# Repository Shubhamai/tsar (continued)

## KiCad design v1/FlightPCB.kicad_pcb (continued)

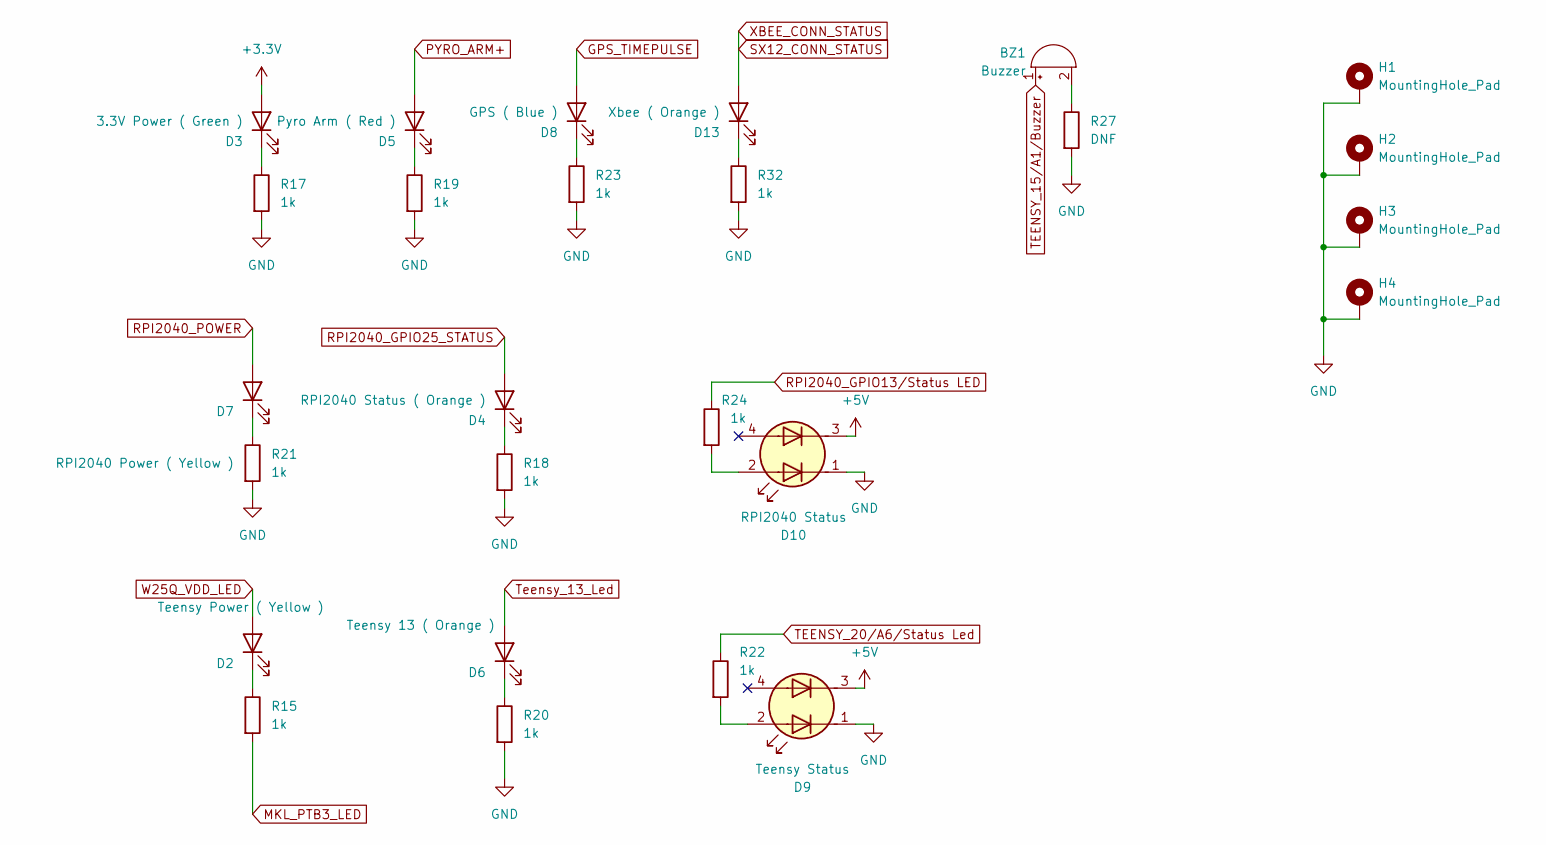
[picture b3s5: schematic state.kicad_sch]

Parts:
BZ1: Buzzer; Buzzer_CUI_CPT-9019S-SMT
D2: Teensy Power ( Yellow ); LED_0402_1005Metric
D3: 3.3V Power ( Green ); LED_0402_1005Metric
D4: RPI2040 Status ( Orange ); LED_0402_1005Metric
D5: Pyro Arm ( Red ); LED_0402_1005Metric
D6: Teensy 13 ( Orange ); LED_0402_1005Metric
D7: RPI2040 Power ( Yellow ); LED_0402_1005Metric
D8: GPS ( Blue ); LED_0402_1005Metric
D9: Teensy Status; IN-PI22TAT5R5G5B
D10: RPI2040 Status; IN-PI22TAT5R5G5B
D13: Xbee ( Orange ); LED_0402_1005Metric
H1, H2, H3, H4: MountingHole_Pad; MountingHole_2.7mm_M2.5_Pad_Via
R15, R17, R18, R19, R20, R21, R22, R23, R24, R32: 1k; R_0603_1608Metric
R27: DNF; R_0603_1608Metric

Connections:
+3.3V: D3.2 (A); also elsewhere on the board
+5V: D9.3 (A2), D10.3 (A2); also elsewhere on the board
BARO_SCK/Teensy: D6.2 (A); also elsewhere on the board
BatteryTerminal-: D9.1 (A1), D10.1 (A1), H1.1, H2.1, H3.1, H4.1, R17.2, R18.2, R19.2, R20.2, R21.2, R23.2, R27.2, R32.2; also elsewhere on the board
GPS_TIMEPULSE: D8.2 (A); also elsewhere on the board
MKL_PTB3_LED: R15.2; also elsewhere on the board
unnamed: BZ1.2 (-), R27.1
unnamed: D2.1 (K), R15.1
unnamed: D3.1 (K), R17.1
unnamed: D4.1 (K), R18.1
unnamed: D5.1 (K), R19.1
unnamed: D6.1 (K), R20.1
unnamed: D7.1 (K), R21.1
unnamed: D8.1 (K), R23.1
unnamed: D9.2 (K1), R22.2
unnamed: D10.2 (K1), R24.2
unnamed: D13.1 (K), R32.1
PYRO_ARM+: D5.2 (A); also elsewhere on the board
RPI2040_GPIO13/Status LED: R24.1; also elsewhere on the board
RPI2040_GPIO25_STATUS: D4.2 (A); also elsewhere on the board
RPI2040_POWER: D7.2 (A); also elsewhere on the board
SX12_CONN_STATUS: D13.2 (A); also elsewhere on the board
TEENSY_15/A1/Buzzer: BZ1.1 (+); also elsewhere on the board
TEENSY_20/A6: R22.1; also elsewhere on the board
W25Q_VDD_LED: D2.2 (A); also elsewhere on the board

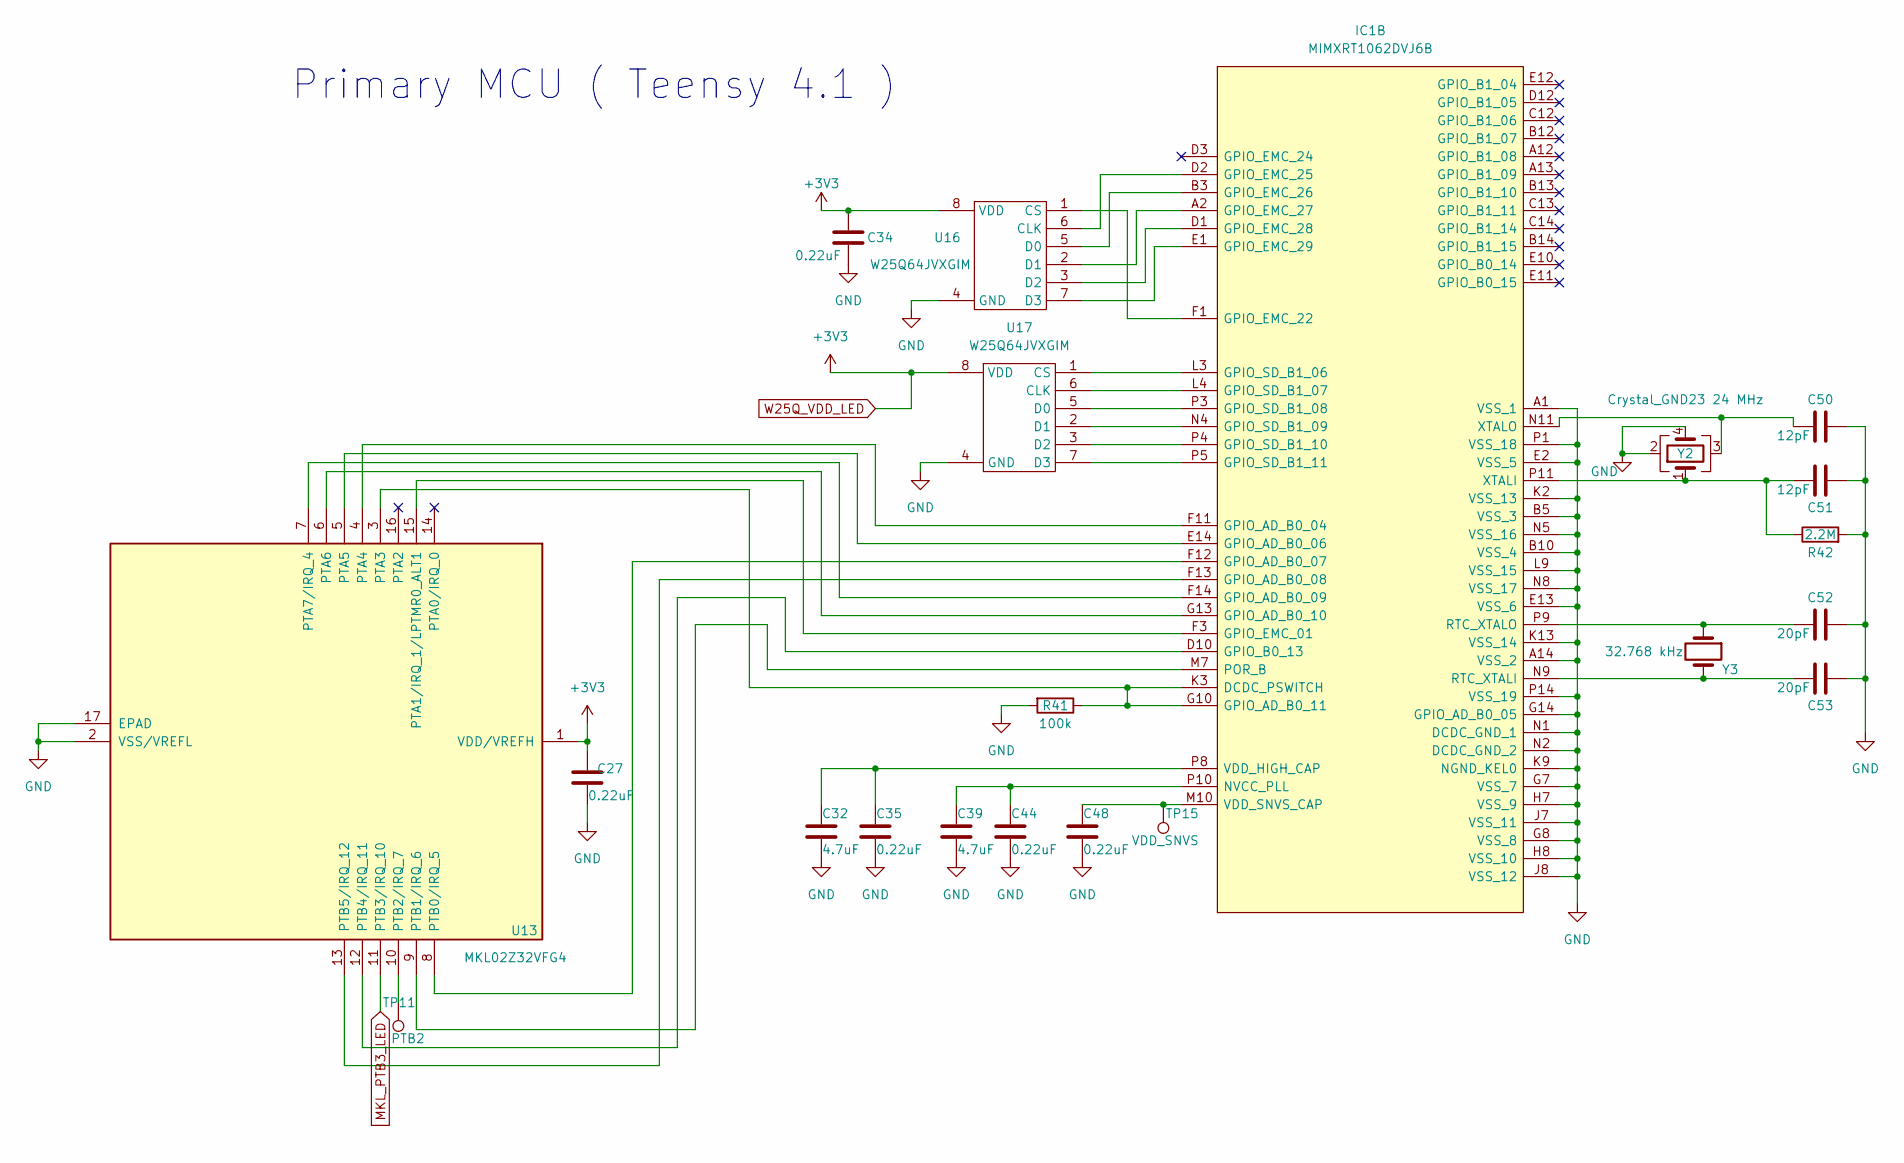
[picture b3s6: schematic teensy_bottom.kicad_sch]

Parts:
C27, C34, C35, C44, C48: 0.22uF; C_0402_1005Metric
C32, C39: 4.7uF; C_0603_1608Metric
C50, C51: 12pF; C_0402_1005Metric
C52, C53: 20pF; C_0402_1005Metric
IC1: MIMXRT1062DVJ6B; BGA196C80P14X14_1200X1200X152; Mouser Part Number 771-MIMXRT1062DVJ6B
R41: 100k; R_0603_1608Metric
R42: 2.2M; R_0603_1608Metric
TP11: PTB2; TestPoint_Pad_D1.0mm
TP15: VDD_SNVS; TestPoint_Pad_D1.0mm
U13: MKL02Z32VFG4; QFN-16-1EP_3x3mm_P0.5mm_EP1.9x1.9mm
U16, U17: W25Q64JVXGIM; XSON8_4x4mm
Y2: Crystal_GND23 24 MHz; Crystal_SMD_Abracon_ABM3B-4Pin_5.0x3.2mm
Y3: 32.768 kHz; Crystal_SMD_2012-2Pin_2.0x1.2mm

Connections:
BatteryTerminal-: C27.2, C32.2, C34.2, C35.2, C39.2, C44.2, C48.2, C50.2, C51.2, C52.2, C53.2, IC1.A1 (VSS_1), IC1.A14 (VSS_2), IC1.B5 (VSS_3), IC1.B10 (VSS_4), IC1.E2 (VSS_5), IC1.E13 (VSS_6), IC1.G7 (VSS_7), IC1.G8 (VSS_8), IC1.G14 (GPIO_AD_B0_05), IC1.H7 (VSS_9), IC1.H8 (VSS_10), IC1.J7 (VSS_11), IC1.J8 (VSS_12), IC1.K2 (VSS_13), IC1.K9 (NGND_KEL0), IC1.K13 (VSS_14), IC1.L9 (VSS_15), IC1.N1 (DCDC_GND_1), IC1.N2 (DCDC_GND_2), IC1.N5 (VSS_16), IC1.N8 (VSS_17), IC1.P1 (VSS_18), IC1.P14 (VSS_19), R41.2, R42.2, U13.2 (VSS/VREFL), U13.17 (EPAD), U16.4 (GND), U17.4 (GND), Y2.2, Y2.4; also elsewhere on the board
MKL_PTB3_LED: U13.11 (PTB3/IRQ_10); also elsewhere on the board
unnamed: IC1.G10 (GPIO_AD_B0_11), IC1.K3 (DCDC_PSWITCH), R41.1, U13.3 (PTA3)
unnamed: IC1.F11 (GPIO_AD_B0_04), U13.4 (PTA4)
unnamed: IC1.E14 (GPIO_AD_B0_06), U13.5 (PTA5)
unnamed: IC1.F12 (GPIO_AD_B0_07), U13.8 (PTB0/IRQ_5)
unnamed: IC1.F13 (GPIO_AD_B0_08), U13.13 (PTB5/IRQ_12)
unnamed: IC1.F14 (GPIO_AD_B0_09), U13.7 (PTA7/IRQ_4)
unnamed: IC1.G13 (GPIO_AD_B0_10), U13.6 (PTA6)
unnamed: IC1.D10 (GPIO_B0_13), U13.12 (PTB4/IRQ_11)
unnamed: IC1.F3 (GPIO_EMC_01), U13.15 (PTA1/IRQ_1/LPTMR0_ALT1)
unnamed: IC1.F1 (GPIO_EMC_22), U16.1 (CS)
unnamed: IC1.D2 (GPIO_EMC_25), U16.6 (CLK)
unnamed: IC1.B3 (GPIO_EMC_26), U16.5 (D0)
unnamed: IC1.A2 (GPIO_EMC_27), U16.2 (D1)
unnamed: IC1.D1 (GPIO_EMC_28), U16.3 (D2)
unnamed: IC1.E1 (GPIO_EMC_29), U16.7 (D3)
unnamed: IC1.L3 (GPIO_SD_B1_06), U17.1 (CS)
unnamed: IC1.L4 (GPIO_SD_B1_07), U17.6 (CLK)
unnamed: IC1.P3 (GPIO_SD_B1_08), U17.5 (D0)
unnamed: IC1.N4 (GPIO_SD_B1_09), U17.2 (D1)
unnamed: IC1.P4 (GPIO_SD_B1_10), U17.3 (D2)
unnamed: IC1.P5 (GPIO_SD_B1_11), U17.7 (D3)
unnamed: C39.1, C44.1, IC1.P10 (NVCC_PLL)
unnamed: IC1.M7 (POR_B), U13.9 (PTB1/IRQ_6)
unnamed: C53.1, IC1.N9 (RTC_XTALI), Y3.2
unnamed: C52.1, IC1.P9 (RTC_XTALO), Y3.1
unnamed: C32.1, C35.1, IC1.P8 (VDD_HIGH_CAP)
unnamed: C48.1, IC1.M10 (VDD_SNVS_CAP), TP15.1
unnamed: C51.1, IC1.P11 (XTALI), R42.1, Y2.1
unnamed: C50.1, IC1.N11 (XTALO), Y2.3
unnamed: TP11.1, U13.10 (PTB2/IRQ_7)
W25Q_VDD_LED: C27.1, C34.1, U13.1 (VDD/VREFH), U16.8 (VDD), U17.8 (VDD); also elsewhere on the board

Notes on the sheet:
Primary MCU ( Teensy 4.1 )

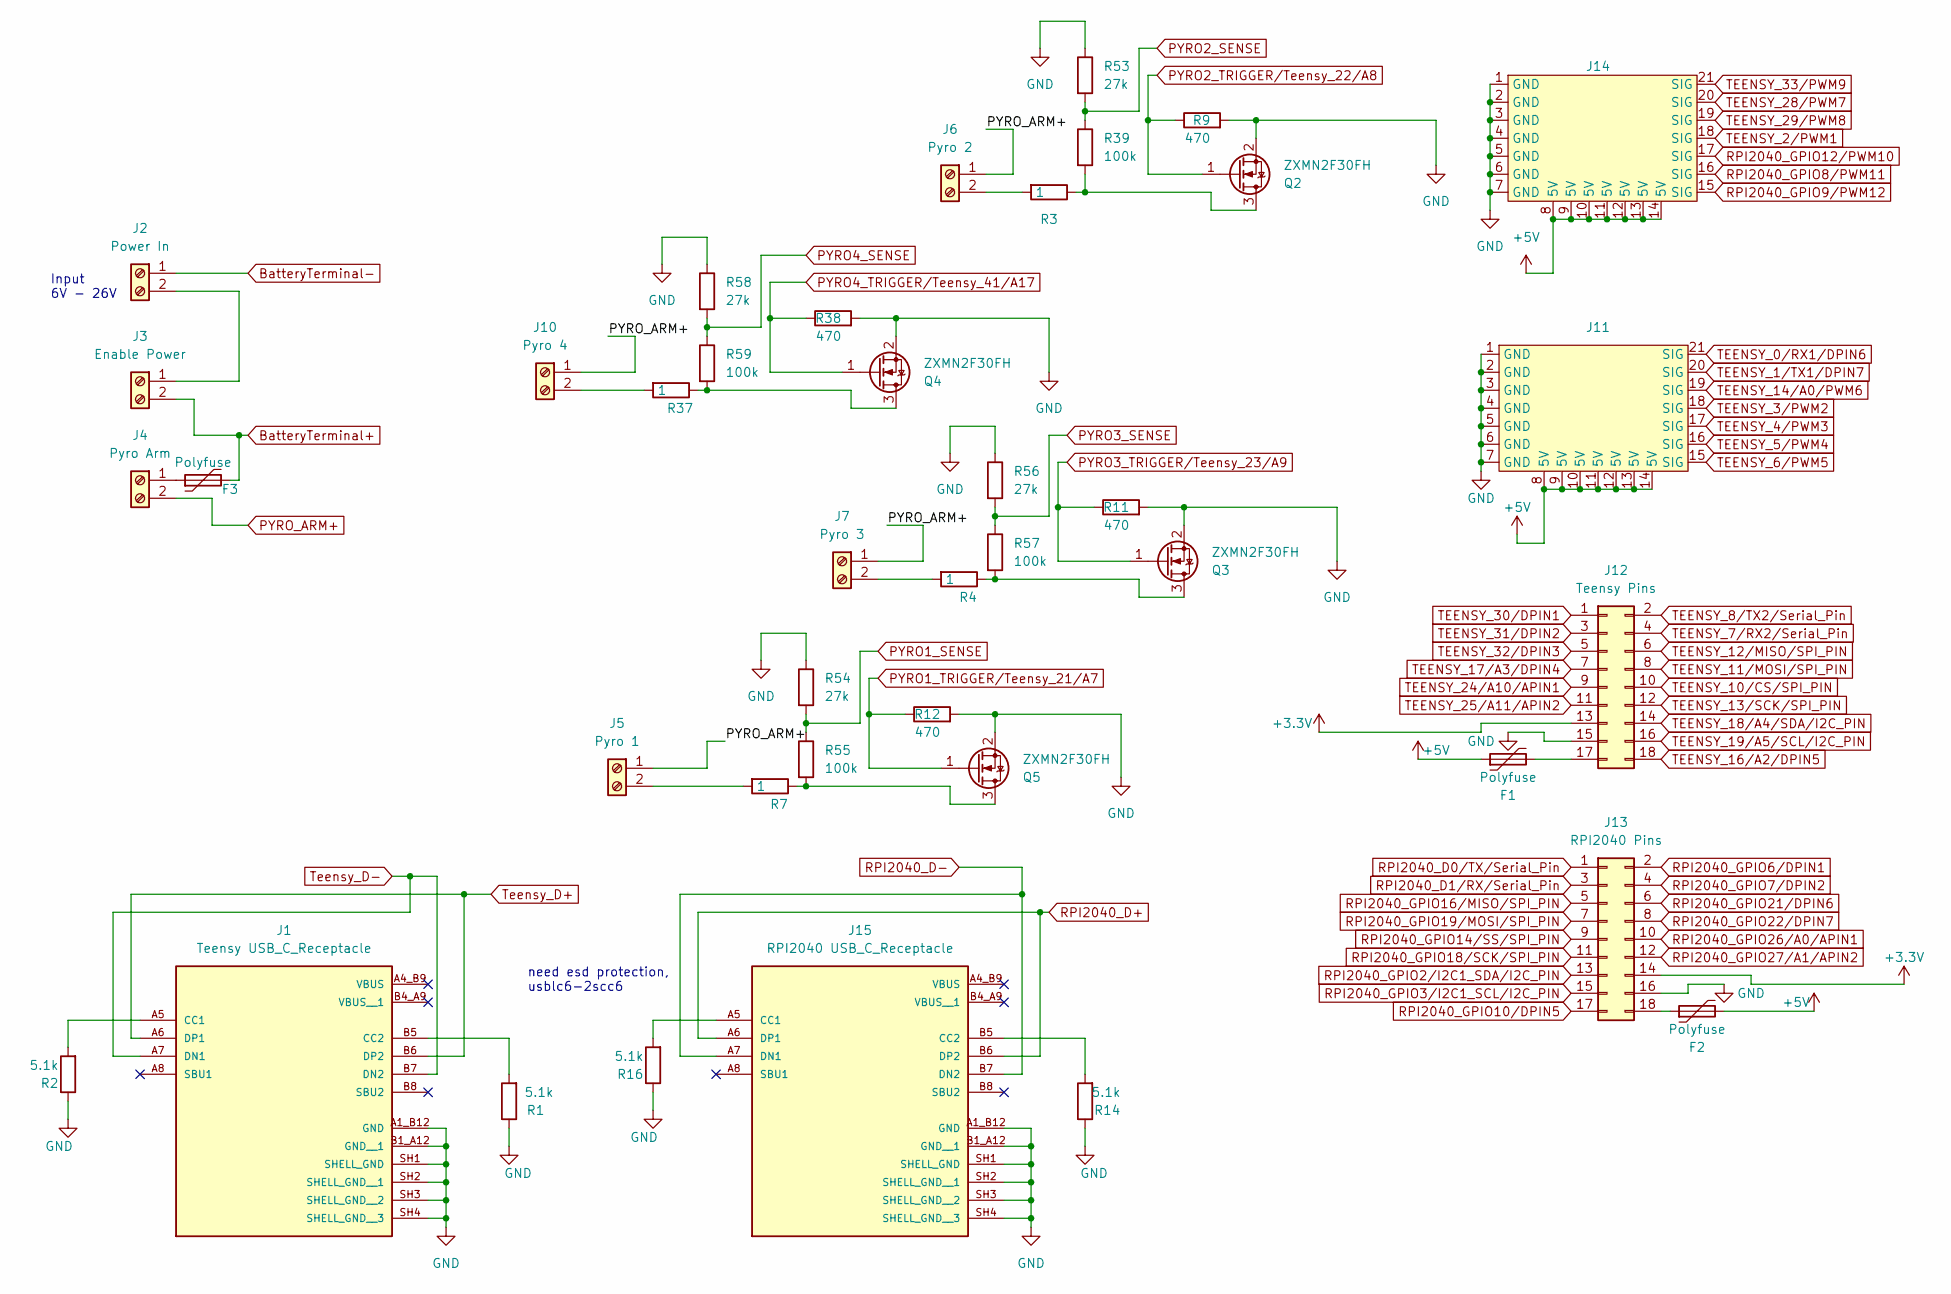
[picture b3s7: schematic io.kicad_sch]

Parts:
F1, F2: Polyfuse; Fuse_1206_3216Metric
F3: Polyfuse; Fuse_1812_4532Metric
J1: Teensy USB_C_Receptacle; GCT_USB4105-GF-A; PARTREV B3
J2: Power In; TerminalBlock_Phoenix_PT-1,5-2-5.0-H_1x02_P5.00mm_Horizontal
J3: Enable Power; TerminalBlock_Phoenix_PT-1,5-2-5.0-H_1x02_P5.00mm_Horizontal
J4: Pyro Arm; TerminalBlock_Phoenix_PT-1,5-2-5.0-H_1x02_P5.00mm_Horizontal
J5: Pyro 1; TerminalBlock_Phoenix_PT-1,5-2-5.0-H_1x02_P5.00mm_Horizontal
J6: Pyro 2; TerminalBlock_Phoenix_PT-1,5-2-5.0-H_1x02_P5.00mm_Horizontal
J7: Pyro 3; TerminalBlock_Phoenix_PT-1,5-2-5.0-H_1x02_P5.00mm_Horizontal
J10: Pyro 4; TerminalBlock_Phoenix_PT-1,5-2-5.0-H_1x02_P5.00mm_Horizontal
J11: PinHeader_3x05_P2.54mm_Vertical_Left
J12: Teensy Pins; PinSocket_2x09_P2.54mm_Vertical
J13: RPI2040 Pins; PinSocket_2x09_P2.54mm_Vertical
J14: PinHeader_3x05_P2.54mm_Vertical_Right
J15: RPI2040 USB_C_Receptacle; GCT_USB4105-GF-A; PARTREV B3
Q2, Q3, Q4, Q5: ZXMN2F30FH; SOT-23
R1, R2, R14, R16: 5.1k; R_0603_1608Metric
R3, R4, R7, R37: 1; R_0603_1608Metric
R9, R11, R12, R38: 470; R_0603_1608Metric
R39, R55, R57, R59: 100k; R_0603_1608Metric
R53, R54, R56, R58: 27k; R_0603_1608Metric

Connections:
+3.3V: J12.13, J13.14; also elsewhere on the board
+5V: F1.1, F2.2, J11.8 (5V), J11.9 (5V), J11.10 (5V), J11.11 (5V), J11.12 (5V), J11.13 (5V), J11.14 (5V), J14.8 (5V), J14.9 (5V), J14.10 (5V), J14.11 (5V), J14.12 (5V), J14.13 (5V), J14.14 (5V); also elsewhere on the board
BARO_MISO/Teensy: J12.6; also elsewhere on the board
BARO_MOSI/Teensy: J12.8; also elsewhere on the board
BARO_SCK/Teensy: J12.12; also elsewhere on the board
BatteryTerminal+: F3.2, J3.2; also elsewhere on the board
BatteryTerminal-: J1.A1_B12 (GND), J1.B1_A12 (GND__1), J1.SH1 (SHELL_GND), J1.SH2 (SHELL_GND__1), J1.SH3 (SHELL_GND__2), J1.SH4 (SHELL_GND__3), J2.1, J11.1 (GND), J11.2 (GND), J11.3 (GND), J11.4 (GND), J11.5 (GND), J11.6 (GND), J11.7 (GND), J12.15, J13.16, J14.1 (GND), J14.2 (GND), J14.3 (GND), J14.4 (GND), J14.5 (GND), J14.6 (GND), J14.7 (GND), J15.A1_B12 (GND), J15.B1_A12 (GND__1), J15.SH1 (SHELL_GND), J15.SH2 (SHELL_GND__1), J15.SH3 (SHELL_GND__2), J15.SH4 (SHELL_GND__3), Q2.2 (S), Q3.2 (S), Q4.2 (S), Q5.2 (S), R1.1, R2.1, R9.2, R11.2, R12.2, R14.1, R16.1, R38.2, R53.1, R54.1, R56.1, R58.1; also elsewhere on the board
unnamed: J1.A5 (CC1), R2.2
unnamed: J1.B5 (CC2), R1.2
unnamed: J2.2, J3.1
unnamed: F3.1, J4.1
unnamed: J5.2, R7.2
unnamed: J6.2, R3.2
unnamed: J7.2, R4.2
unnamed: J10.2, R37.2
unnamed: F1.2, J12.17
unnamed: F2.1, J13.18
unnamed: J15.A5 (CC1), R16.2
unnamed: J15.B5 (CC2), R14.2
unnamed: Q2.3 (D), R3.1, R39.2
unnamed: Q3.3 (D), R4.1, R57.2
unnamed: Q4.3 (D), R37.1, R59.2
unnamed: Q5.3 (D), R7.1, R55.2
PYRO1_SENSE: R54.2, R55.1; also elsewhere on the board
PYRO1_TRIGGER/Teensy_21/A7: Q5.1 (G), R12.1; also elsewhere on the board
PYRO2_SENSE: R39.1, R53.2; also elsewhere on the board
PYRO2_TRIGGER/Teensy_22/A8: Q2.1 (G), R9.1; also elsewhere on the board
PYRO3_SENSE: R56.2, R57.1; also elsewhere on the board
PYRO3_TRIGGER/Teensy_23/A9: Q3.1 (G), R11.1; also elsewhere on the board
PYRO4_SENSE: R58.2, R59.1; also elsewhere on the board
PYRO4_TRIGGER/Teensy_41/A17: Q4.1 (G), R38.1; also elsewhere on the board
PYRO_ARM+: J4.2, J5.1, J6.1, J7.1, J10.1; also elsewhere on the board
RPI2040_D0/TX/Serial_Pin: J13.1; also elsewhere on the board
RPI2040_D1/RX/Serial_Pin: J13.3; also elsewhere on the board
RPI2040_D+: J15.A6 (DP1), J15.B6 (DP2); also elsewhere on the board
RPI2040_D-: J15.A7 (DN1), J15.B7 (DN2); also elsewhere on the board
RPI2040_GPIO2/I2C1_SDA/I2C_PIN: J13.13; also elsewhere on the board
RPI2040_GPIO3/I2C1_SCL/I2C_PIN: J13.15; also elsewhere on the board
RPI2040_GPIO6/DPIN1: J13.2; also elsewhere on the board
RPI2040_GPIO7/DPIN2: J13.4; also elsewhere on the board
RPI2040_GPIO8/PWM11: J14.16 (SIG); also elsewhere on the board
RPI2040_GPIO9/PWM12: J14.15 (SIG); also elsewhere on the board
RPI2040_GPIO10/DPIN5: J13.17; also elsewhere on the board
RPI2040_GPIO12/PWM10: J14.17 (SIG); also elsewhere on the board
RPI2040_GPIO14/SS/SPI_PIN: J13.9; also elsewhere on the board
RPI2040_GPIO16/MISO/SPI_PIN: J13.5; also elsewhere on the board
RPI2040_GPIO18/SCK/SPI_PIN: J13.11; also elsewhere on the board
RPI2040_GPIO19/MOSI/SPI_PIN: J13.7; also elsewhere on the board
RPI2040_GPIO21/DPIN6: J13.6; also elsewhere on the board
RPI2040_GPIO22/DPIN7: J13.8; also elsewhere on the board
RPI2040_GPIO26/A0/APIN1: J13.10; also elsewhere on the board
RPI2040_GPIO27/A1/APIN2: J13.12; also elsewhere on the board
TEENSY_0/RX1: J11.21 (SIG); also elsewhere on the board
TEENSY_1/TX1: J11.20 (SIG); also elsewhere on the board
TEENSY_2/PWM1: J14.18 (SIG); also elsewhere on the board
TEENSY_3/PWM2: J11.18 (SIG); also elsewhere on the board
TEENSY_4/PWM3: J11.17 (SIG); also elsewhere on the board
TEENSY_5/PWM4: J11.16 (SIG); also elsewhere on the board
TEENSY_6/PWM5: J11.15 (SIG); also elsewhere on the board
TEENSY_7/RX2/Serial_Pin: J12.4; also elsewhere on the board
TEENSY_8/TX2/Serial_Pin: J12.2; also elsewhere on the board
TEENSY_10/CS/SPI_PIN: J12.10; also elsewhere on the board
TEENSY_14/A0/PWM6: J11.19 (SIG); also elsewhere on the board
TEENSY_16/A2: J12.18; also elsewhere on the board
TEENSY_17/A3: J12.7; also elsewhere on the board
TEENSY_18/A4/SDA/I2C_PIN: J12.14; also elsewhere on the board
TEENSY_19/A5/SCL/I2C_PIN: J12.16; also elsewhere on the board
TEENSY_24/A10: J12.9; also elsewhere on the board
TEENSY_25/A11: J12.11; also elsewhere on the board
TEENSY_28/PWM7: J14.20 (SIG); also elsewhere on the board
TEENSY_29/PWM8: J14.19 (SIG); also elsewhere on the board
TEENSY_30/DPIN1: J12.1; also elsewhere on the board
TEENSY_31/DPIN2: J12.3; also elsewhere on the board
TEENSY_32/DPIN3: J12.5; also elsewhere on the board
TEENSY_33/PWM9: J14.21 (SIG); also elsewhere on the board
Teensy_D+: J1.A6 (DP1), J1.B6 (DP2); also elsewhere on the board
Teensy_D-: J1.A7 (DN1), J1.B7 (DN2); also elsewhere on the board

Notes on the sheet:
need esd protection, usblc6-2scc6
Input 6V - 26V

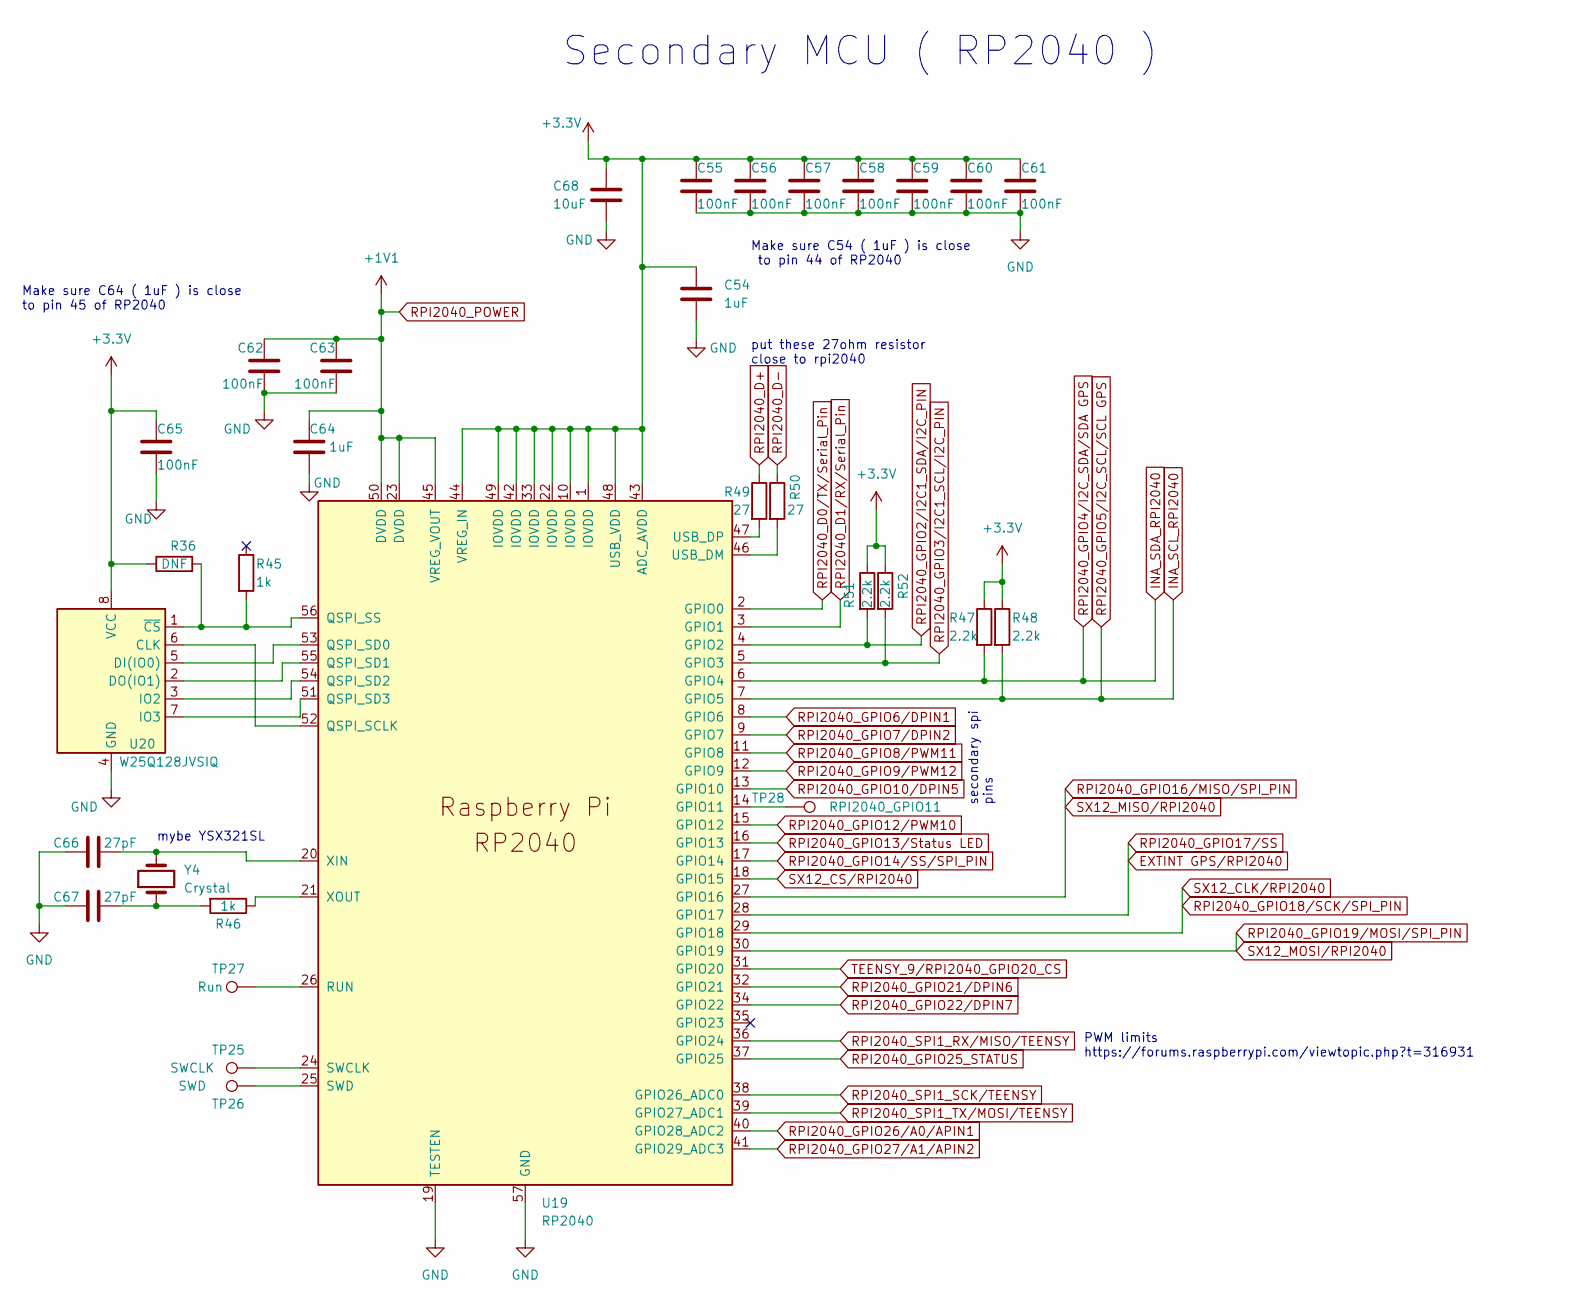
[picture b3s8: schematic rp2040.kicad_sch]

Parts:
C54, C64: 1uF; C_0603_1608Metric
C55, C56, C57, C58, C59, C60, C61, C62, C63, C65: 100nF; C_0603_1608Metric
C66, C67: 27pF; C_0603_1608Metric
C68: 10uF; C_0603_1608Metric
R36: DNF; R_0603_1608Metric
R45, R46: 1k; R_0603_1608Metric
R47, R48, R51, R52: 2.2k; R_0603_1608Metric
R49, R50: 27; R_0603_1608Metric
TP25: SWCLK; TestPoint_Pad_D1.0mm
TP26: SWD; TestPoint_Pad_D1.0mm
TP27: Run; TestPoint_Pad_D1.0mm
TP28: RPI2040_GPIO11; TestPoint_Pad_D1.0mm
U19: RP2040; RP2040-QFN-56
U20: W25Q128JVSIQ; SOIC-8_5.23x5.23mm_P1.27mm
Y4: Crystal; Crystal_SMD_Abracon_ABM8G-4Pin_3.2x2.5mm

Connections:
+3.3V: C54.1, C55.1, C56.1, C57.1, C58.1, C59.1, C60.1, C61.1, C65.1, C68.1, R36.1, R47.1, R48.1, R51.1, R52.1, U19.1 (IOVDD), U19.10 (IOVDD), U19.22 (IOVDD), U19.33 (IOVDD), U19.42 (IOVDD), U19.43 (ADC_AVDD), U19.44 (VREG_IN), U19.48 (USB_VDD), U19.49 (IOVDD), U20.8 (VCC); also elsewhere on the board
BARO_MISO/Teensy: U19.36 (GPIO24); also elsewhere on the board
BARO_MOSI/Teensy: U19.39 (GPIO27_ADC1); also elsewhere on the board
BARO_SCK/Teensy: U19.38 (GPIO26_ADC0); also elsewhere on the board
BatteryTerminal-: C54.2, C55.2, C56.2, C57.2, C58.2, C59.2, C60.2, C61.2, C62.2, C63.2, C64.2, C65.2, C66.1, C67.2, C68.2, U19.19 (TESTEN), U19.57 (GND), U20.4 (GND); also elsewhere on the board
EXTINT GPS/RPI2040: U19.28 (GPIO17); also elsewhere on the board
INA_SCL_RPI2040: R48.2, U19.7 (GPIO5); also elsewhere on the board
INA_SDA_RPI2040: R47.2, U19.6 (GPIO4); also elsewhere on the board
unnamed: C67.1, R46.2, Y4.1
unnamed: TP28.1, U19.14 (GPIO11)
unnamed: U19.52 (QSPI_SCLK), U20.6 (CLK)
unnamed: U19.53 (QSPI_SD0), U20.5 (DI(IO0))
unnamed: U19.55 (QSPI_SD1), U20.2 (DO(IO1))
unnamed: U19.54 (QSPI_SD2), U20.3 (IO2)
unnamed: U19.51 (QSPI_SD3), U20.7 (IO3)
unnamed: R36.2, R45.2, U19.56 (QSPI_SS), U20.1 (~CS)
unnamed: TP27.1, U19.26 (RUN)
unnamed: TP25.1, U19.24 (SWCLK)
unnamed: TP26.1, U19.25 (SWD)
unnamed: R50.2, U19.46 (USB_DM)
unnamed: R49.2, U19.47 (USB_DP)
unnamed: C66.2, U19.20 (XIN), Y4.2
unnamed: R46.1, U19.21 (XOUT)
RPI2040_D0/TX/Serial_Pin: U19.2 (GPIO0); also elsewhere on the board
RPI2040_D1/RX/Serial_Pin: U19.3 (GPIO1); also elsewhere on the board
RPI2040_D+: R49.1; also elsewhere on the board
RPI2040_D-: R50.1; also elsewhere on the board
RPI2040_GPIO2/I2C1_SDA/I2C_PIN: R51.2, U19.4 (GPIO2); also elsewhere on the board
RPI2040_GPIO3/I2C1_SCL/I2C_PIN: R52.2, U19.5 (GPIO3); also elsewhere on the board
RPI2040_GPIO6/DPIN1: U19.8 (GPIO6); also elsewhere on the board
RPI2040_GPIO7/DPIN2: U19.9 (GPIO7); also elsewhere on the board
RPI2040_GPIO8/PWM11: U19.11 (GPIO8); also elsewhere on the board
RPI2040_GPIO9/PWM12: U19.12 (GPIO9); also elsewhere on the board
RPI2040_GPIO10/DPIN5: U19.13 (GPIO10); also elsewhere on the board
RPI2040_GPIO12/PWM10: U19.15 (GPIO12); also elsewhere on the board
RPI2040_GPIO13/Status LED: U19.16 (GPIO13); also elsewhere on the board
RPI2040_GPIO14/SS/SPI_PIN: U19.17 (GPIO14); also elsewhere on the board
RPI2040_GPIO16/MISO/SPI_PIN: U19.27 (GPIO16); also elsewhere on the board
RPI2040_GPIO18/SCK/SPI_PIN: U19.29 (GPIO18); also elsewhere on the board
RPI2040_GPIO19/MOSI/SPI_PIN: U19.30 (GPIO19); also elsewhere on the board
RPI2040_GPIO21/DPIN6: U19.32 (GPIO21); also elsewhere on the board
RPI2040_GPIO22/DPIN7: U19.34 (GPIO22); also elsewhere on the board
RPI2040_GPIO25_STATUS: U19.37 (GPIO25); also elsewhere on the board
RPI2040_GPIO26/A0/APIN1: U19.40 (GPIO28_ADC2); also elsewhere on the board
RPI2040_GPIO27/A1/APIN2: U19.41 (GPIO29_ADC3); also elsewhere on the board
RPI2040_POWER: C62.1, C63.1, C64.1, U19.23 (DVDD), U19.45 (VREG_VOUT), U19.50 (DVDD); also elsewhere on the board
SX12_CS/RPI2040: U19.18 (GPIO15); also elsewhere on the board
TEENSY_9/RPI2040_GPIO20_CS: U19.31 (GPIO20); also elsewhere on the board

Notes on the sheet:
mybe YSX321SL
PWM limits https://forums.raspberrypi.com/viewtopic.php?t=316931
secondary spi pins
put these 27ohm resistor close to rpi2040
Make sure C54 ( 1uF ) is close to pin 44 of RP2040
Secondary MCU ( RP2040 )
Make sure C64 ( 1uF ) is close to pin 45 of RP2040

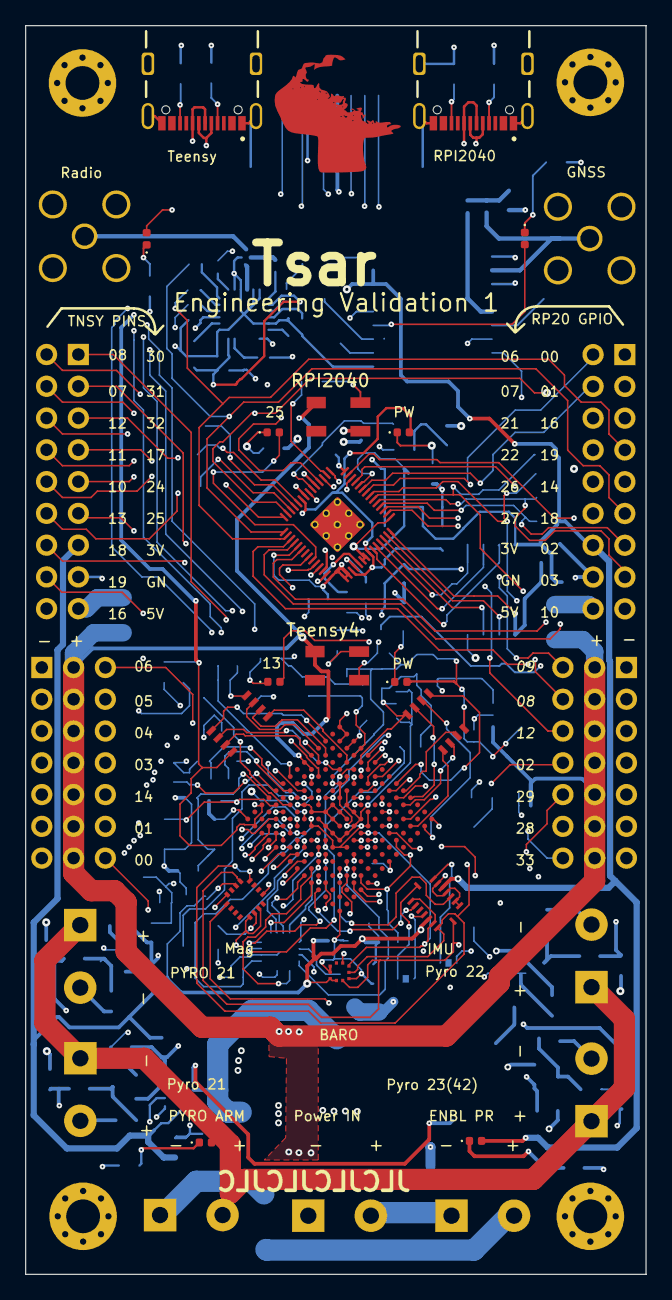
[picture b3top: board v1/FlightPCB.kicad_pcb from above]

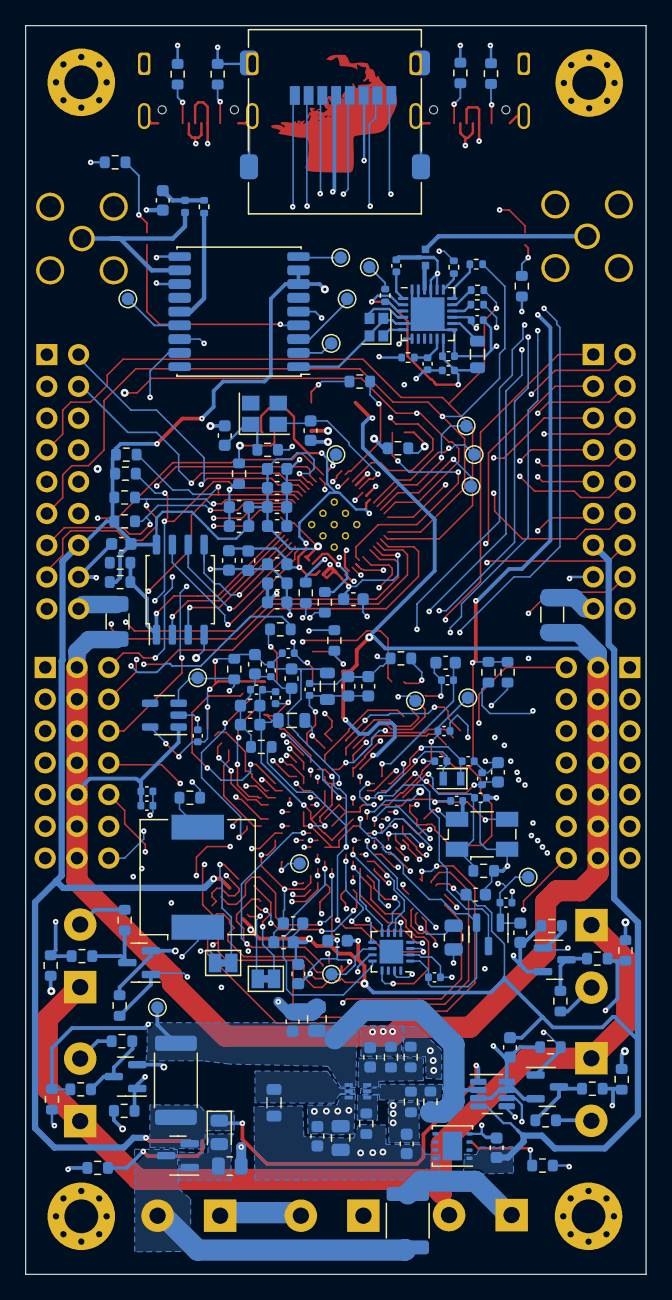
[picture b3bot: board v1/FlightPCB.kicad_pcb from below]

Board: 4 copper layers, 49.6 x 99.8 mm, 204 parts (168 on the bottom side), 198 nets.
